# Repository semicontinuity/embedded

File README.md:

Embedded projects.
================================================================================

Projects for AVR microcontrollers.
--------------------------------------------------------------------------------
- [Primitive alarm](../../tree/master/target/alarm-a)
- [Primitive terminal](../../tree/master/target/display)
- [Voltage relay](../../tree/master/target/voltage-relay)
- [Mood lamp - firmware under development](../../tree/master/target/mood-lamp)
- [Primitive motion sensor controller, that works in pair with primitive alarm](../../tree/master/target/motion-sensor-controller/firmware/main)
- [Servo controller - unfinished, no firmware yet](../../tree/master/target/motor-controller/hardware)
- [LED dimmer, controlled via CAN bus](../../tree/master/target/plc-3u-a/firmware/network-led-dimmer)
- [CAN bus router - firmware under development](../../tree/master/target/plc-6u-a/firmware/can_router)
- [Roller shutter controller, controlled via CAN bus](../../tree/master/target/roller-shutter-controller/firmware/main)
- [Humidity meter](../../tree/master/target/plc-3u-b/firmware/humidity-meter)

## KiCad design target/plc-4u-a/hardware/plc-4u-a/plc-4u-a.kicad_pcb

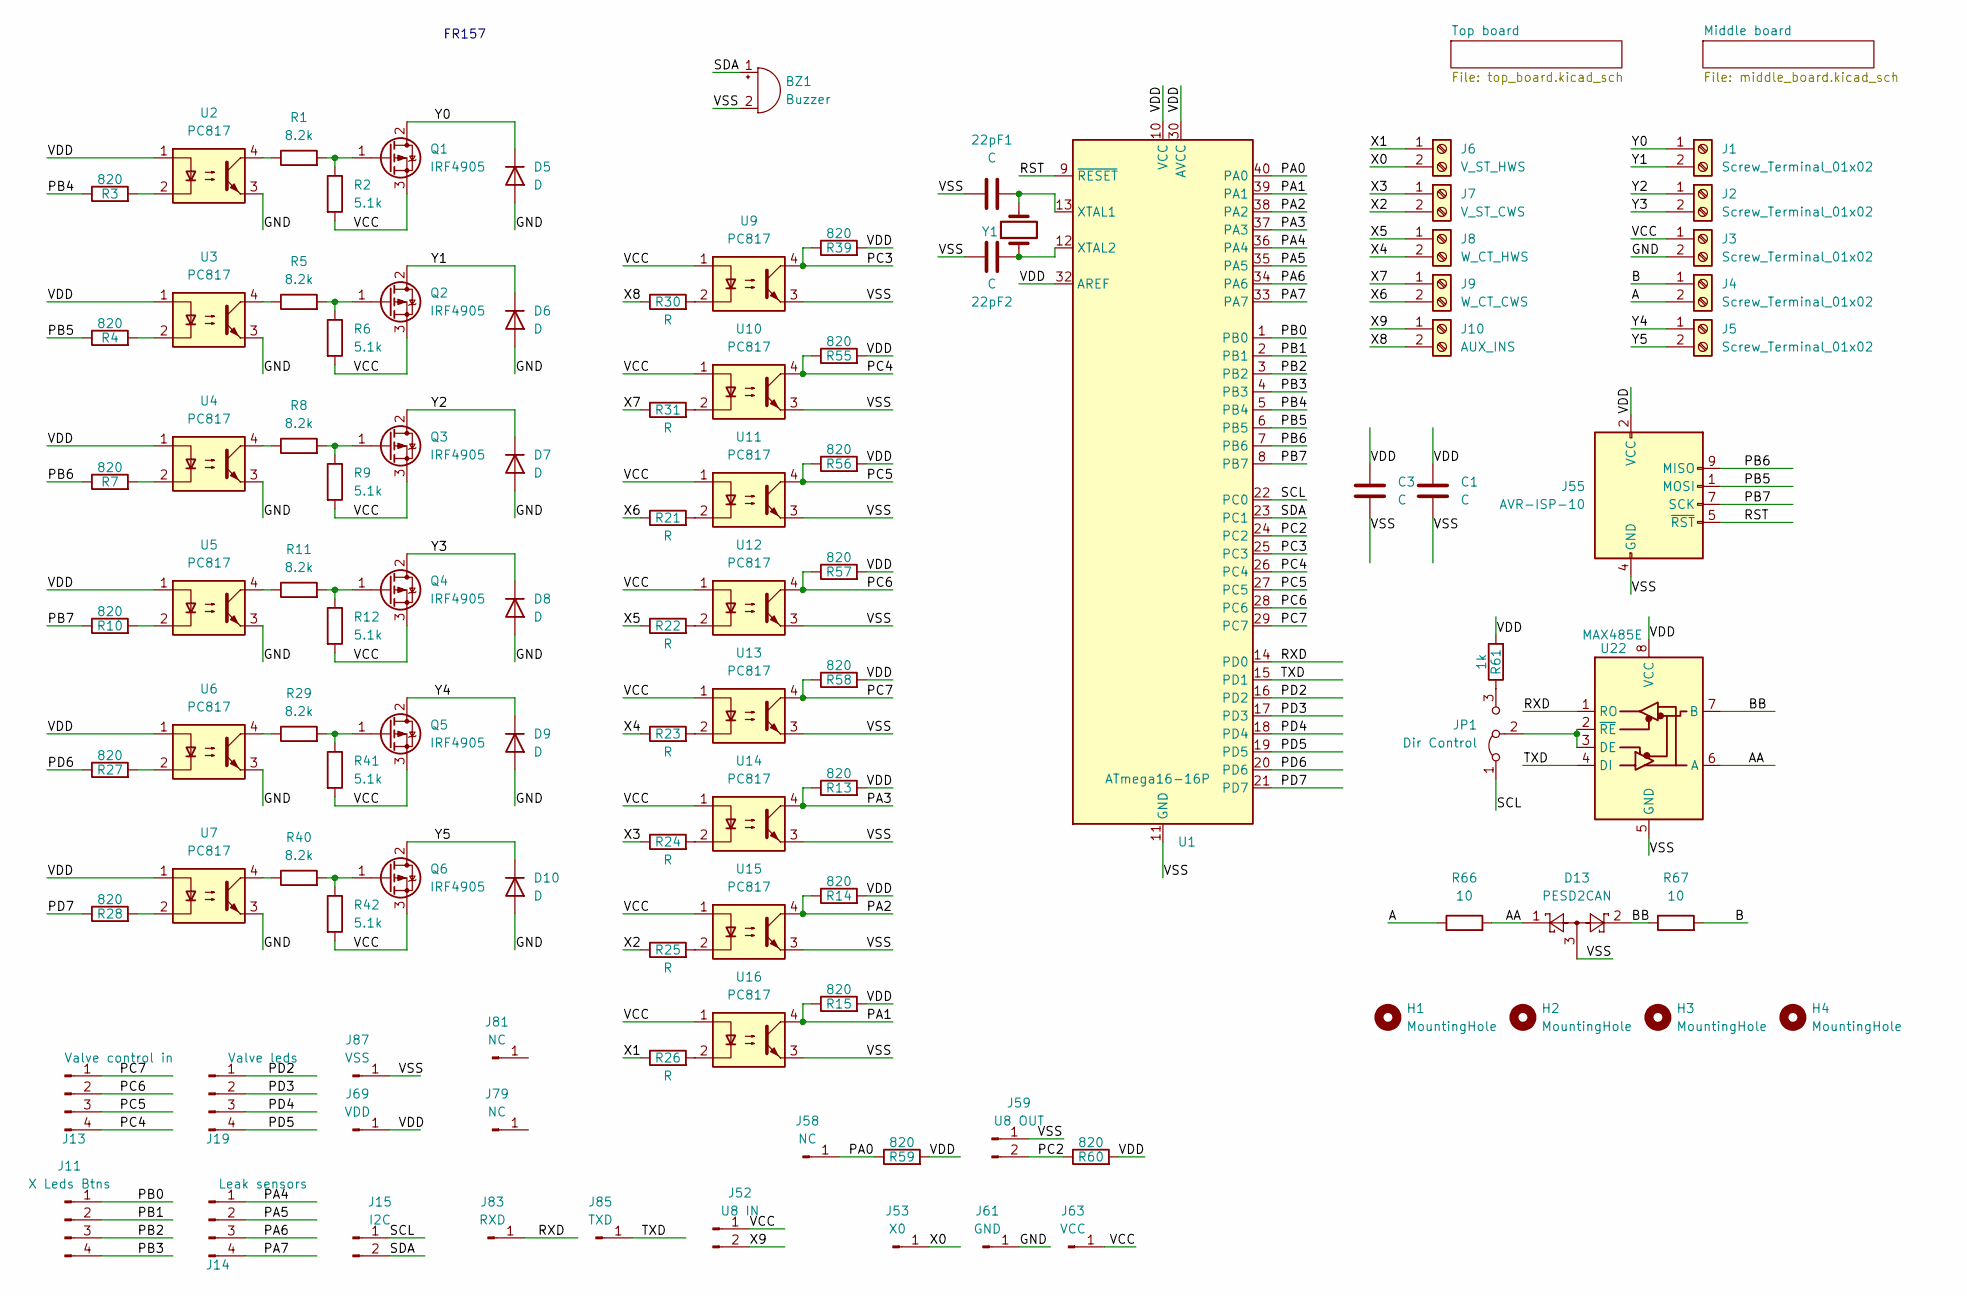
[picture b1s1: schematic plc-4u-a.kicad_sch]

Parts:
22pF1, 22pF2: C; C_0805_2012Metric
BZ1: Buzzer; Buzzer_12x9.5RM7.6
C1, C3: C; C_0805_2012Metric
D5, D6, D7, D8, D9, D10: D; D_DO-41_SOD81_P10.16mm_Horizontal
D13: PESD2CAN; SOT-23
H1, H2, H3, H4: MountingHole; MountingHole_3.2mm_M3
J1, J2, J3, J4, J5: Screw_Terminal_01x02; TerminalBlock_Phoenix_MKDS-1,5-2-5.08_1x02_P5.08mm_Horizont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
J6: V_ST_HWS; TerminalBlock_Phoenix_MKDS-1,5-2-5.08_1x02_P5.08mm_Horizont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
J7: V_ST_CWS; TerminalBlock_Phoenix_MKDS-1,5-2-5.08_1x02_P5.08mm_Horizont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
J8: W_CT_HWS; TerminalBlock_Phoenix_MKDS-1,5-2-5.08_1x02_P5.08mm_Horizont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
J9: W_CT_CWS; TerminalBlock_Phoenix_MKDS-1,5-2-5.08_1x02_P5.08mm_Horizont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
J10: AUX_INS; TerminalBlock_Phoenix_MKDS-1,5-2-5.08_1x02_P5.08mm_Horizont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
J11: X Leds Btns; PinHeader_1x04_P2.54mm_Vertical
J13: Valve control in; PinHeader_1x04_P2.54mm_Vertical
J14: Leak sensors; PinHeader_1x04_P2.54mm_Vertical
J15: I2C; PinHeader_1x02_P2.54mm_Vertical
J19: Valve leds; PinHeader_1x04_P2.54mm_Vertical
J52: U8 IN; PinHeader_1x02_P2.54mm_Vertical
J53: X0; PinHeader_1x01_P2.54mm_Vertical
J55: AVR-ISP-10; IDC-Header_2x05_P2.54mm_Vertical
J58, J79, J81: NC; PinHeader_1x01_P2.54mm_Vertical
J59: U8 OUT; PinHeader_1x02_P2.54mm_Vertical
J61: GND; PinHeader_1x01_P2.54mm_Vertical
J63: VCC; PinHeader_1x01_P2.54mm_Vertical
J69: VDD; PinHeader_1x01_P2.54mm_Vertical
J83: RXD; PinHeader_1x01_P2.54mm_Vertical
J85: TXD; PinHeader_1x01_P2.54mm_Vertical
J87: VSS; PinHeader_1x01_P2.54mm_Vertical
JP1: Dir Control; SolderJumper-3_P1.3mm_Bridged2Bar12_Pad1.0x1.5mm
Q1, Q2, Q3, Q4, Q5, Q6: IRF4905; TO-220-3_Vertical
R1, R5, R8, R11, R29, R40: 8.2k; R_0805_2012Metric
R2, R6, R9, R12, R41, R42: 5.1k; R_0805_2012Metric
R3, R4, R7, R10, R13, R14, R15, R27, R28, R39, R55, R56, R57, R58, R59, R60: 820; R_0805_2012Metric
R21, R22, R23, R24, R25, R26, R30, R31: R; R_1206_3216Metric
R61: 1k; R_0805_2012Metric
R66, R67: 10; R_1206_3216Metric
U1: ATmega16-16P; DIP-40_W15.24mm
U2, U3, U4, U5, U6, U7, U9, U10, U11, U12, U13, U14, U15, U16: PC817; DIP-4_W7.62mm
U22: MAX485E; SOIC-8_3.9x4.9mm_P1.27mm
Y1: Crystal; Crystal_HC49-4H_Vertical

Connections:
/A: J4.2, R66.1
/AA: D13.1, R66.2, U22.6 (A)
/B: J4.1, R67.2
/BB: D13.2, R67.1, U22.7 (B)
/GND: D5.2 (A), D6.2 (A), D7.2 (A), D8.2 (A), D9.2 (A), D10.2 (A), J3.2, J61.1, U2.3, U3.3, U4.3, U5.3, U6.3, U7.3
/PA0: J58.1, R59.1, U1.40 (PA0)
/PA1: R15.1, U1.39 (PA1), U16.4
/PA2: R14.1, U1.38 (PA2), U15.4
/PA3: R13.1, U1.37 (PA3), U14.4
/PA4: J14.1, U1.36 (PA4)
/PA5: J14.2, U1.35 (PA5)
/PA6: J14.3, U1.34 (PA6)
/PA7: J14.4, U1.33 (PA7)
/PB0: J11.1, U1.1 (PB0)
/PB1: J11.2, U1.2 (PB1)
/PB2: J11.3, U1.3 (PB2)
/PB3: J11.4, U1.4 (PB3)
/PB4: R3.1, U1.5 (PB4)
/PB5: J55.1 (MOSI), R4.1, U1.6 (PB5)
/PB6: J55.9 (MISO), R7.1, U1.7 (PB6)
/PB7: J55.7 (SCK), R10.1, U1.8 (PB7)
/PC2: J59.2, R60.1, U1.24 (PC2)
/PC3: R39.1, U1.25 (PC3), U9.4
/PC4: J13.4, R55.1, U1.26 (PC4), U10.4
/PC5: J13.3, R56.1, U1.27 (PC5), U11.4
/PC6: J13.2, R57.1, U1.28 (PC6), U12.4
/PC7: J13.1, R58.1, U1.29 (PC7), U13.4
/PD2: J19.1, U1.16 (PD2)
/PD3: J19.2, U1.17 (PD3)
/PD4: J19.3, U1.18 (PD4)
/PD5: J19.4, U1.19 (PD5)
/PD6: R27.1, U1.20 (PD6)
/PD7: R28.1, U1.21 (PD7)
/RST: J55.5 (~RST), U1.9 (~RESET)
/RXD: J83.1, U1.14 (PD0), U22.1 (RO)
/SCL: J15.1, JP1.1 (A), U1.22 (PC0)
/SDA: BZ1.1 (-), J15.2, U1.23 (PC1)
/TXD: J85.1, U1.15 (PD1), U22.4 (DI)
/VCC: J3.1, J52.1, J63.1, Q1.3 (S), Q2.3 (S), Q3.3 (S), Q4.3 (S), Q5.3 (S), Q6.3 (S), R2.2, R6.2, R9.2, R12.2, R41.2, R42.2, U9.1, U10.1, U11.1, U12.1, U13.1, U14.1, U15.1, U16.1
/VDD: C1.1, C3.1, J55.2 (VCC), J69.1, R13.2, R14.2, R15.2, R39.2, R55.2, R56.2, R57.2, R58.2, R59.2, R60.2, R61.2, U1.10 (VCC), U1.30 (AVCC), U1.32 (AREF), U2.1, U3.1, U4.1, U5.1, U6.1, U7.1, U22.8 (VCC)
/VSS: 22pF1.1, 22pF2.1, BZ1.2 (+), C1.2, C3.2, D13.3, J55.4 (GND), J55.6 (GND), J55.8 (GND), J55.10 (GND), J59.1, J87.1, U1.11 (GND), U1.31 (GND), U9.3, U10.3, U11.3, U12.3, U13.3, U14.3, U15.3, U16.3, U22.5 (GND)
/X0: J6.2, J53.1
/X1: J6.1, R26.1
/X2: J7.2, R25.1
/X3: J7.1, R24.1
/X4: J8.2, R23.1
/X5: J8.1, R22.1
/X6: J9.2, R21.1
/X7: J9.1, R31.1
/X8: J10.2, R30.1
/X9: J10.1, J52.2
/Y0: D5.1 (K), J1.1, Q1.2 (D)
/Y1: D6.1 (K), J1.2, Q2.2 (D)
/Y2: D7.1 (K), J2.1, Q3.2 (D)
/Y3: D8.1 (K), J2.2, Q4.2 (D)
/Y4: D9.1 (K), J5.1, Q5.2 (D)
/Y5: D10.1 (K), J5.2, Q6.2 (D)
unnamed: 22pF1.2, U1.13 (XTAL1), Y1.2
unnamed: 22pF2.2, U1.12 (XTAL2), Y1.1
unnamed: JP1.2 (C), U22.2 (~RE), U22.3 (DE)
unnamed: JP1.3 (B), R61.1
unnamed: Q1.1 (G), R1.2, R2.1
unnamed: Q2.1 (G), R5.2, R6.1
unnamed: Q3.1 (G), R8.2, R9.1
unnamed: Q4.1 (G), R11.2, R12.1
unnamed: Q5.1 (G), R29.2, R41.1
unnamed: Q6.1 (G), R40.2, R42.1
unnamed: R1.1, U2.4
unnamed: R3.2, U2.2
unnamed: R4.2, U3.2
unnamed: R5.1, U3.4
unnamed: R7.2, U4.2
unnamed: R8.1, U4.4
unnamed: R10.2, U5.2
unnamed: R11.1, U5.4
unnamed: R21.2, U11.2
unnamed: R22.2, U12.2
unnamed: R23.2, U13.2
unnamed: R24.2, U14.2
unnamed: R25.2, U15.2
unnamed: R26.2, U16.2
unnamed: R27.2, U6.2
unnamed: R28.2, U7.2
unnamed: R29.1, U6.4
unnamed: R30.2, U9.2
unnamed: R31.2, U10.2
unnamed: R40.1, U7.4

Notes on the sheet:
FR157

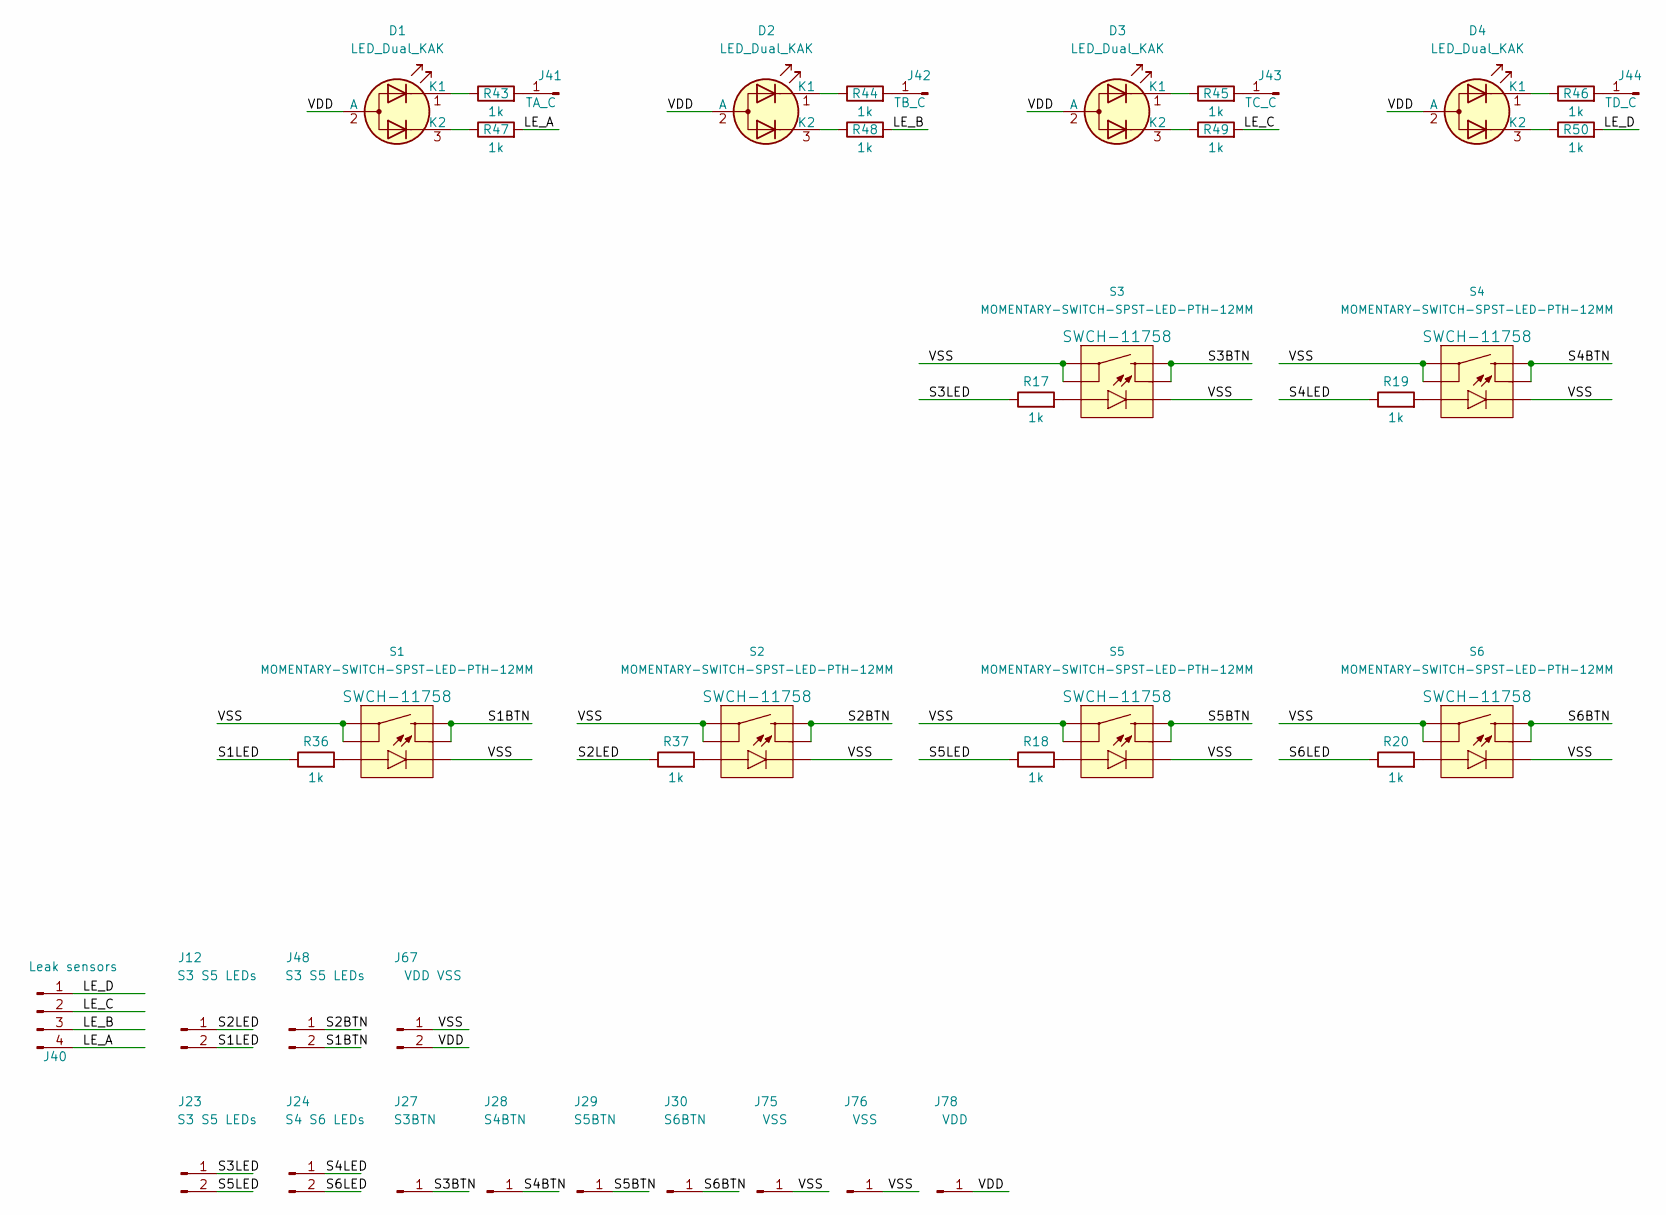
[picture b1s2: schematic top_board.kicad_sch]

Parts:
D1, D2, D3, D4: LED_Dual_KAK; LED_Rectangular_W5.0mm_H2.0mm-3Pins
J12, J23, J48: S3 S5 LEDs; PinHeader_1x02_P2.54mm_Vertical
J24: S4 S6 LEDs; PinHeader_1x02_P2.54mm_Vertical
J27: S3BTN; PinHeader_1x01_P2.54mm_Vertical
J28: S4BTN; PinHeader_1x01_P2.54mm_Vertical
J29: S5BTN; PinHeader_1x01_P2.54mm_Vertical
J30: S6BTN; PinHeader_1x01_P2.54mm_Vertical
J40: Leak sensors; PinHeader_1x04_P2.54mm_Vertical
J41: TA_C; PinHeader_1x01_P2.54mm_Vertical
J42: TB_C; PinHeader_1x01_P2.54mm_Vertical
J43: TC_C; PinHeader_1x01_P2.54mm_Vertical
J44: TD_C; PinHeader_1x01_P2.54mm_Vertical
J67: VDD VSS; PinHeader_1x02_P2.54mm_Vertical
J75, J76: VSS; PinHeader_1x01_P2.54mm_Vertical
J78: VDD; PinHeader_1x01_P2.54mm_Vertical
R17, R18, R19, R20, R36, R37, R43, R44, R45, R46, R47, R48, R49, R50: 1k; R_0805_2012Metric
S1, S2, S3, S4, S5, S6: MOMENTARY-SWITCH-SPST-LED-PTH-12MM; TACTILE_SWITCH_LED_PTH_12MM

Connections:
/Top board/LE_A: J40.4, R47.2
/Top board/LE_B: J40.3, R48.2
/Top board/LE_C: J40.2, R49.2
/Top board/LE_D: J40.1, R50.2
/Top board/S1BTN: J48.2, S1.1, S1.2
/Top board/S1LED: J12.2, R36.1
/Top board/S2BTN: J48.1, S2.1, S2.2
/Top board/S2LED: J12.1, R37.1
/Top board/S3BTN: J27.1, S3.1, S3.2
/Top board/S3LED: J23.1, R17.1
/Top board/S4BTN: J28.1, S4.1, S4.2
/Top board/S4LED: J24.1, R19.1
/Top board/S5BTN: J29.1, S5.1, S5.2
/Top board/S5LED: J23.2, R18.1
/Top board/S6BTN: J30.1, S6.1, S6.2
/Top board/S6LED: J24.2, R20.1
/Top board/VDD: D1.2 (A), D2.2 (A), D3.2 (A), D4.2 (A), J67.2, J78.1
/Top board/VSS: J67.1, J75.1, J76.1, S1.3, S1.4 (1), S1.C, S2.3, S2.4 (1), S2.C, S3.3, S3.4 (1), S3.C, S4.3, S4.4 (1), S4.C, S5.3, S5.4 (1), S5.C, S6.3, S6.4 (1), S6.C
unnamed: D1.1 (K1), R43.1
unnamed: D1.3 (K2), R47.1
unnamed: D2.1 (K1), R44.1
unnamed: D2.3 (K2), R48.1
unnamed: D3.1 (K1), R45.1
unnamed: D3.3 (K2), R49.1
unnamed: D4.1 (K1), R46.1
unnamed: D4.3 (K2), R50.1
unnamed: J41.1, R43.2
unnamed: J42.1, R44.2
unnamed: J43.1, R45.2
unnamed: J44.1, R46.2
unnamed: R17.2, S3.A
unnamed: R18.2, S5.A
unnamed: R19.2, S4.A
unnamed: R20.2, S6.A
unnamed: R36.2, S1.A
unnamed: R37.2, S2.A

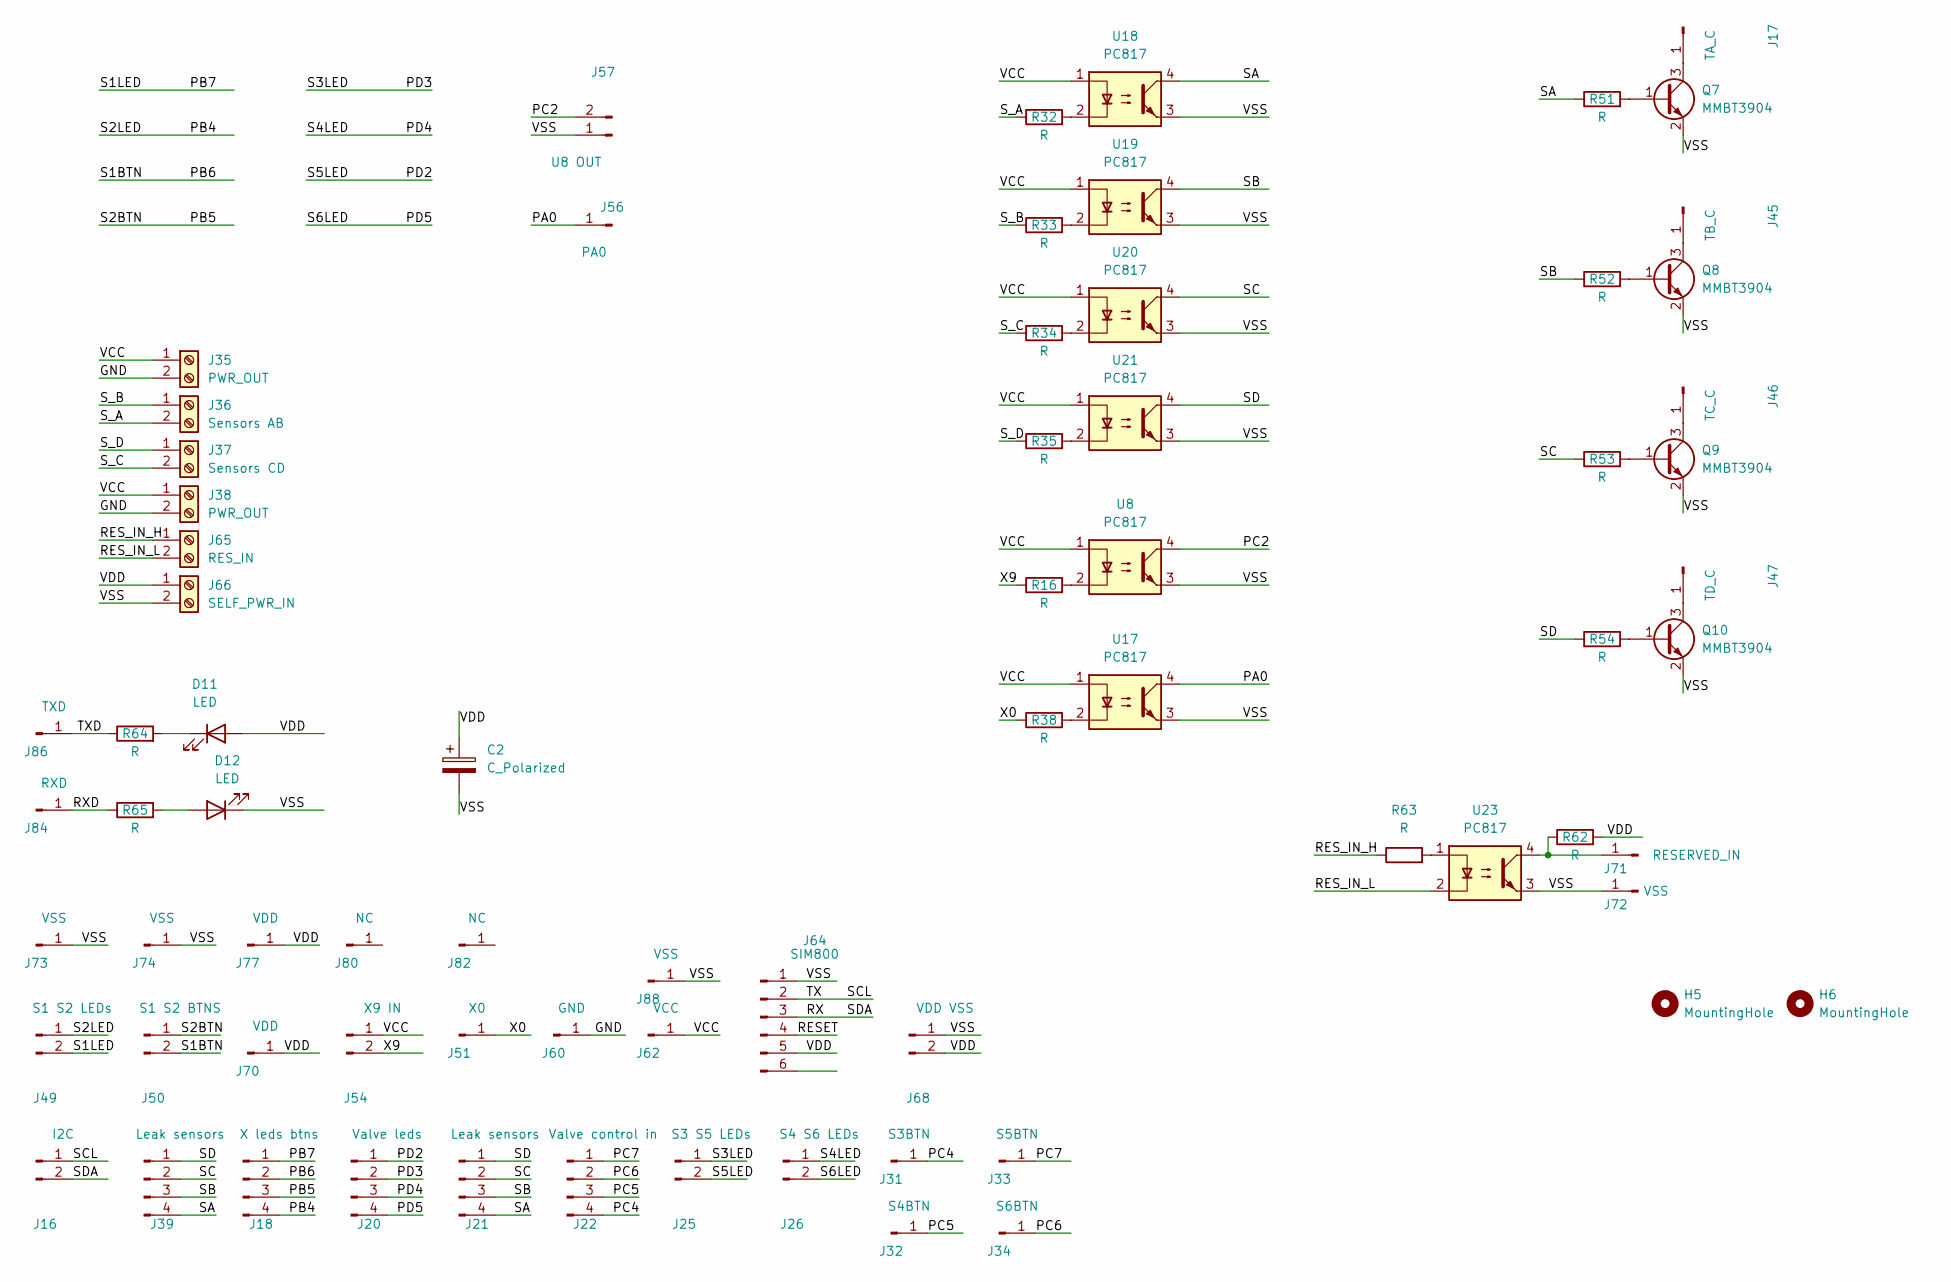
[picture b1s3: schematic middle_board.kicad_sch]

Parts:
C2: C_Polarized; C_1812_4532Metric
D11, D12: LED; LED_D3.0mm
H5, H6: MountingHole; MountingHole_3.2mm_M3
J16: I2C; PinHeader_1x02_P2.54mm_Vertical
J17: TA_C; PinHeader_1x01_P2.54mm_Vertical
J18: X leds btns; PinHeader_1x04_P2.54mm_Vertical
J20: Valve leds; PinHeader_1x04_P2.54mm_Vertical
J21, J39: Leak sensors; PinHeader_1x04_P2.54mm_Vertical
J22: Valve control in; PinHeader_1x04_P2.54mm_Vertical
J25: S3 S5 LEDs; PinHeader_1x02_P2.54mm_Vertical
J26: S4 S6 LEDs; PinHeader_1x02_P2.54mm_Vertical
J31: S3BTN; PinHeader_1x01_P2.54mm_Vertical
J32: S4BTN; PinHeader_1x01_P2.54mm_Vertical
J33: S5BTN; PinHeader_1x01_P2.54mm_Vertical
J34: S6BTN; PinHeader_1x01_P2.54mm_Vertical
J35, J38: PWR_OUT; TerminalBlock_Phoenix_MKDS-1,5-2-5.08_1x02_P5.08mm_Horizont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
J36: Sensors AB; TerminalBlock_Phoenix_MKDS-1,5-2-5.08_1x02_P5.08mm_Horizont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
J37: Sensors CD; TerminalBlock_Phoenix_MKDS-1,5-2-5.08_1x02_P5.08mm_Horizont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
J45: TB_C; PinHeader_1x01_P2.54mm_Vertical
J46: TC_C; PinHeader_1x01_P2.54mm_Vertical
J47: TD_C; PinHeader_1x01_P2.54mm_Vertical
J49: S1 S2 LEDs; PinHeader_1x02_P2.54mm_Vertical
J50: S1 S2 BTNS; PinHeader_1x02_P2.54mm_Vertical
J51: X0; PinHeader_1x01_P2.54mm_Vertical
J54: X9 IN; PinHeader_1x02_P2.54mm_Vertical
J56: PA0; PinHeader_1x01_P2.54mm_Vertical
J57: U8 OUT; PinHeader_1x02_P2.54mm_Vertical
J60: GND; PinHeader_1x01_P2.54mm_Vertical
J62: VCC; PinHeader_1x01_P2.54mm_Vertical
J64: SIM800; PinHeader_1x06_P2.54mm_Vertical
J65: RES_IN; TerminalBlock_Phoenix_MKDS-1,5-2-5.08_1x02_P5.08mm_Horizont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
J66: SELF_PWR_IN; TerminalBlock_Phoenix_MKDS-1,5-2-5.08_1x02_P5.08mm_Horizont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
J68: VDD VSS; PinHeader_1x02_P2.54mm_Vertical
J70, J77: VDD; PinHeader_1x01_P2.54mm_Vertical
J71: RESERVED_IN; PinHeader_1x01_P2.54mm_Vertical
J72, J73, J74, J88: VSS; PinHeader_1x01_P2.54mm_Vertical
J80, J82: NC; PinHeader_1x01_P2.54mm_Vertical
J84: RXD; PinHeader_1x01_P2.54mm_Vertical
J86: TXD; PinHeader_1x01_P2.54mm_Vertical
Q7, Q8, Q9, Q10: MMBT3904; SOT-23
R16, R32, R33, R34, R35, R38: R; R_1206_3216Metric
R51, R52, R53, R54, R62, R64, R65: R; R_0805_2012Metric
R63: R; R_Axial_DIN0309_L9.0mm_D3.2mm_P5.08mm_Vertical
U8, U17, U18, U19, U20, U21, U23: PC817; DIP-4_W7.62mm

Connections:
/Middle board/GND: J35.2, J38.2, J60.1
/Middle board/PA0: J56.1, U17.4
/Middle board/PB4: J18.4, J49.1
/Middle board/PB5: J18.3, J50.1
/Middle board/PB6: J18.2, J50.2
/Middle board/PB7: J18.1, J49.2
/Middle board/PC2: J57.2, U8.4
/Middle board/PC4: J22.4, J31.1
/Middle board/PC5: J22.3, J32.1
/Middle board/PC6: J22.2, J34.1
/Middle board/PC7: J22.1, J33.1
/Middle board/PD2: J20.1, J25.2
/Middle board/PD3: J20.2, J25.1
/Middle board/PD4: J20.3, J26.1
/Middle board/PD5: J20.4, J26.2
/Middle board/RESET: J64.4
/Middle board/RES_IN_H: J65.1, R63.1
/Middle board/RES_IN_L: J65.2, U23.2
/Middle board/RX: J16.2, J64.3
/Middle board/RXD: J84.1, R65.1
/Middle board/SA: J21.4, J39.4, R51.1, U18.4
/Middle board/SB: J21.3, J39.3, R52.1, U19.4
/Middle board/SC: J21.2, J39.2, R53.1, U20.4
/Middle board/SCL: J16.1, J64.2
/Middle board/SD: J21.1, J39.1, R54.1, U21.4
/Middle board/S_A: J36.2, R32.1
/Middle board/S_B: J36.1, R33.1
/Middle board/S_C: J37.2, R34.1
/Middle board/S_D: J37.1, R35.1
/Middle board/TXD: J86.1, R64.1
/Middle board/VCC: J35.1, J38.1, J54.1, J62.1, U8.1, U17.1, U18.1, U19.1, U20.1, U21.1
/Middle board/VDD: C2.1, D11.2 (A), J64.5, J66.1, J68.2, J70.1, J77.1, R62.2
/Middle board/VSS: C2.2, D12.1 (K), J57.1, J64.1, J66.2, J68.1, J72.1, J73.1, J74.1, J88.1, Q7.2 (E), Q8.2 (E), Q9.2 (E), Q10.2 (E), U8.3, U17.3, U18.3, U19.3, U20.3, U21.3, U23.3
/Middle board/X0: J51.1, R38.1
/Middle board/X9: J54.2, R16.1
unnamed: D11.1 (K), R64.2
unnamed: D12.2 (A), R65.2
unnamed: J17.1, Q7.3 (C)
unnamed: J45.1, Q8.3 (C)
unnamed: J46.1, Q9.3 (C)
unnamed: J47.1, Q10.3 (C)
unnamed: J71.1, R62.1, U23.4
unnamed: Q7.1 (B), R51.2
unnamed: Q8.1 (B), R52.2
unnamed: Q9.1 (B), R53.2
unnamed: Q10.1 (B), R54.2
unnamed: R16.2, U8.2
unnamed: R32.2, U18.2
unnamed: R33.2, U19.2
unnamed: R34.2, U20.2
unnamed: R35.2, U21.2
unnamed: R38.2, U17.2
unnamed: R63.2, U23.1

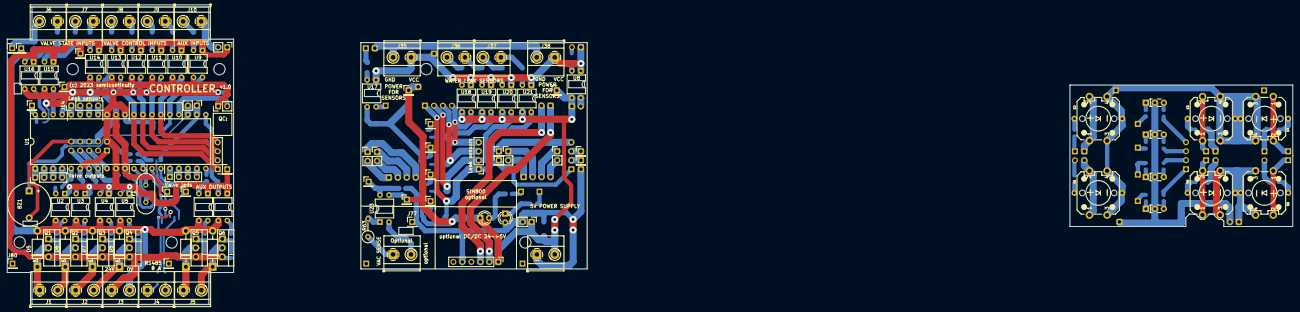
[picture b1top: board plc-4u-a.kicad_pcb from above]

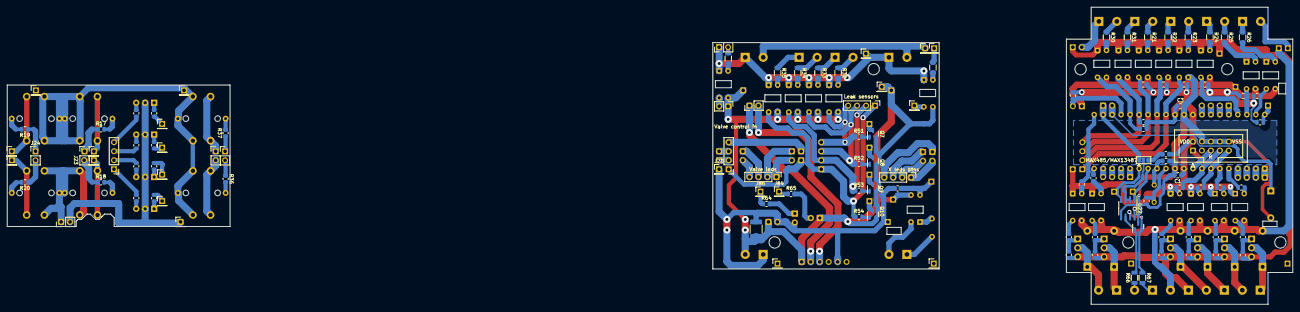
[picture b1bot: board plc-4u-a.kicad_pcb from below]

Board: 2 copper layers, 363.5 x 84.0 mm, 221 parts (113 on the bottom side), 175 nets.

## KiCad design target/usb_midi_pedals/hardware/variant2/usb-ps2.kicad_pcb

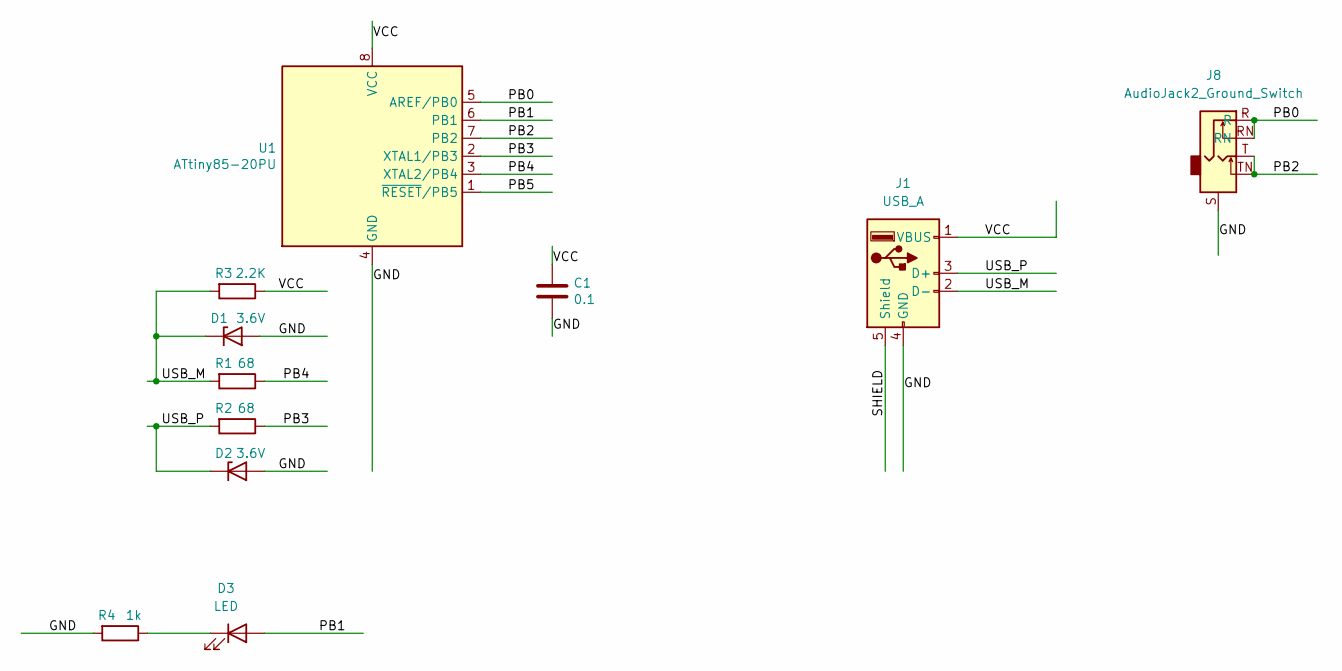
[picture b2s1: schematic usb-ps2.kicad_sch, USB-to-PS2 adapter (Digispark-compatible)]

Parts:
C1: 0.1; C_0805_2012Metric_Pad1.18x1.45mm_HandSolder
D1, D2: 3.6V; D_DO-34_SOD68_P7.62mm_Horizontal
D3: LED; LED_D3.0mm
J1: USB_A; USB_A_CONNFLY_DS1095-WNR0
J8: AudioJack2_Ground_Switch; Jack_3.5mm_CUI_SJ1-3525N_Horizontal
R1, R2: 68; R_Axial_DIN0204_L3.6mm_D1.6mm_P7.62mm_Horizontal
R3: 2.2K; R_0805_2012Metric_Pad1.20x1.40mm_HandSolder
R4: 1k; R_0805_2012Metric_Pad1.20x1.40mm_HandSolder
U1: ATtiny85-20PU; DIP-8_W7.62mm

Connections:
/GND: C1.2, D1.2 (A), D2.2 (A), J1.4 (GND), J8.S, R4.2, U1.4 (GND)
/PB0: J8.R, J8.RN, U1.5 (AREF/PB0)
/PB1: D3.2 (A), U1.6 (PB1)
/PB2: J8.T, J8.TN, U1.7 (PB2)
/PB3: R2.1, U1.2 (XTAL1/PB3)
/PB4: R1.1, U1.3 (XTAL2/PB4)
/PB5: U1.1 (~RESET/PB5)
/SHIELD: J1.5 (Shield)
/USB_M: D1.1 (K), J1.2 (D-), R1.2, R3.2
/USB_P: D2.1 (K), J1.3 (D+), R2.2
/VCC: C1.1, J1.1 (VBUS), R3.1, U1.8 (VCC)
unnamed: D3.1 (K), R4.1

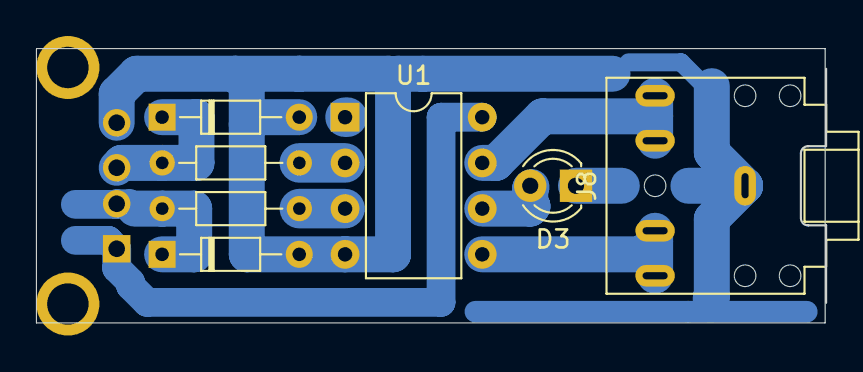
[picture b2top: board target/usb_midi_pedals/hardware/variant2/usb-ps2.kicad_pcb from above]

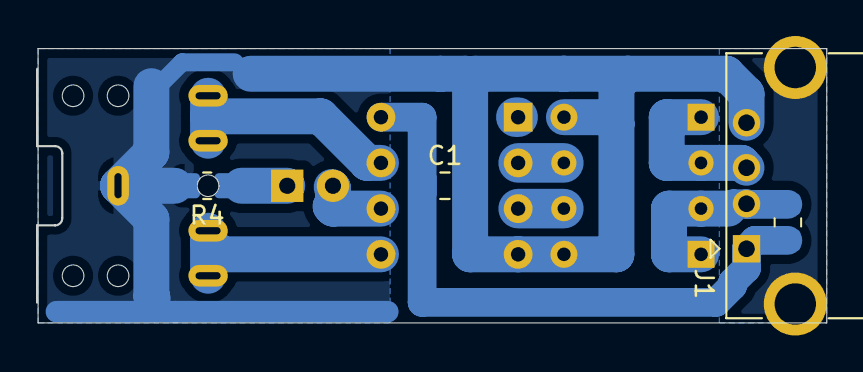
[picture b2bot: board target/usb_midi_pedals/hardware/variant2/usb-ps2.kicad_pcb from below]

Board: 2 copper layers, 43.8 x 15.2 mm, 11 parts (4 on the bottom side), 10 nets.

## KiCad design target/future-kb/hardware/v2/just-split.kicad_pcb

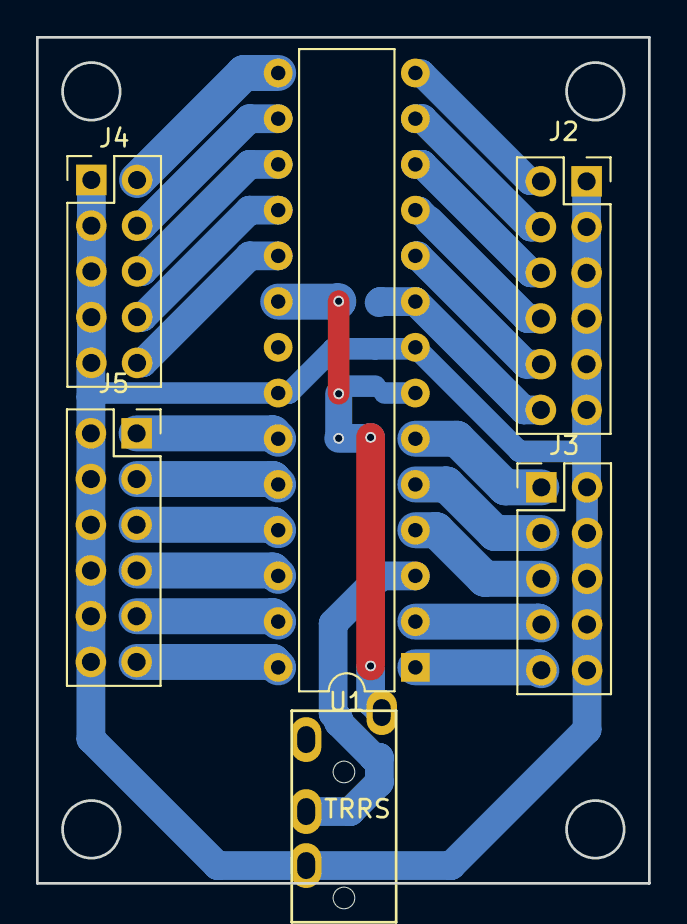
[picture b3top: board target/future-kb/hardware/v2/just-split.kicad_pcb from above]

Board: 2 copper layers, 34.0 x 47.0 mm, 7 parts (1 on the bottom side), 25 nets.

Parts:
C1: 0.1; C_0805_2012Metric_Pad1.18x1.45mm_HandSolder
J1: MJ-4PP-9; MJ-4PP-9_1side
J2, J5: Conn_02x06_Odd_Even; PinSocket_2x06_P2.54mm_Vertical
J3, J4: Conn_02x05_Odd_Even; PinHeader_2x05_P2.54mm_Vertical
U1: ATmega88-20PU; DIP-28_W7.62mm

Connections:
/PB0: J2.2, U1.14 (PB0)
/PB1: J4.2, U1.15 (PB1)
/PB2: J4.4, U1.16 (PB2)
/PB3: J4.6, U1.17 (PB3)
/PB4: J4.8, U1.18 (PB4)
/PB5: J4.10, U1.19 (PB5)
/PB6: J2.12, U1.9 (XTAL1/PB6)
/PB7: J2.10, U1.10 (XTAL2/PB7)
/PC0: J5.1, U1.23 (PC0)
/PC1: J5.3, U1.24 (PC1)
/PC2: J5.5, U1.25 (PC2)
/PC3: J5.7, U1.26 (PC3)
/PC4: J5.9, U1.27 (PC4)
/PC5: J5.11, U1.28 (PC5)
/PD2: J3.5, U1.4 (PD2)
/PD3: J3.3, U1.5 (PD3)
/PD4: J3.1, U1.6 (PD4)
/PD5: J2.8, U1.11 (PD5)
/PD6: J2.6, U1.12 (PD6)
/PD7: J2.4, U1.13 (PD7)
/RESET: J3.9, U1.1 (~RESET/PC6)
/RXD: J3.7, U1.2 (PD0)
/VCC: C1.1, J1.A, U1.7 (VCC), U1.20 (AVCC)
GND: C1.2, J1.B, J2.1, J2.3, J2.5, J2.7, J2.9, J2.11, J3.2, J3.4, J3.6, J3.8, J3.10, J4.1, J4.3, J4.5, J4.7, J4.9, J5.2, J5.4, J5.6, J5.8, J5.10, J5.12, U1.8 (GND), U1.22 (GND)
TXD: J1.C, U1.3 (PD1)

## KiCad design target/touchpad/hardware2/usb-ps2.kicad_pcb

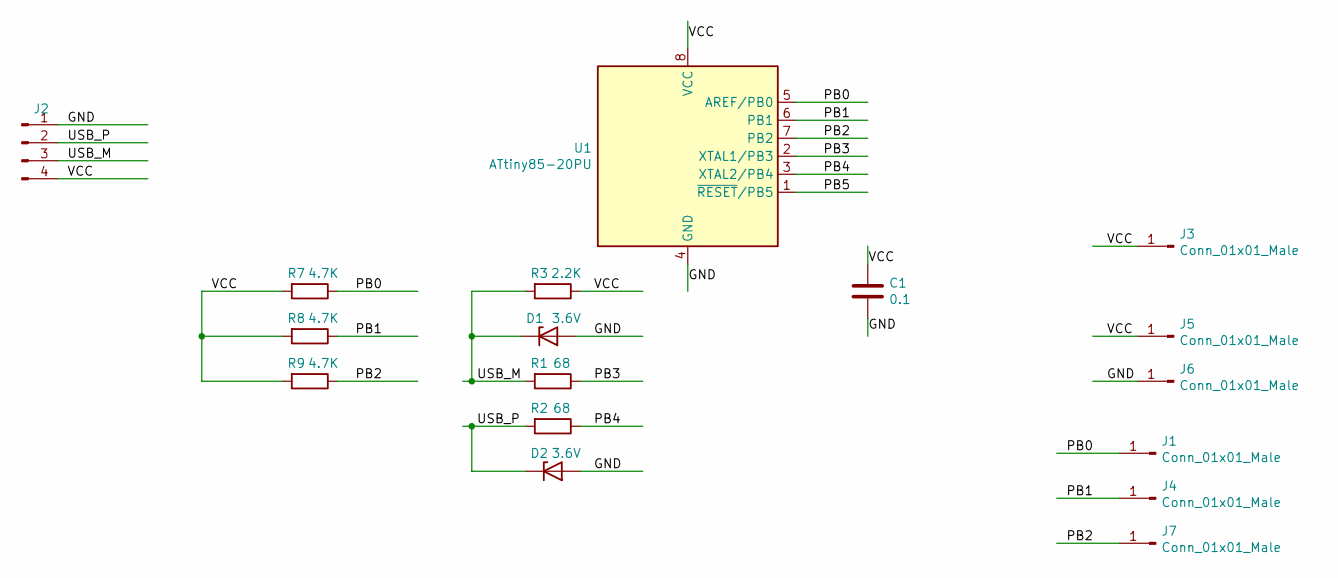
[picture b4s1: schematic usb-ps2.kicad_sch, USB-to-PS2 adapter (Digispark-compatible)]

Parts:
C1: 0.1; C_0805_2012Metric_Pad1.18x1.45mm_HandSolder
D1, D2: 3.6V; D_DO-34_SOD68_P7.62mm_Horizontal
J1, J3, J4, J5, J6, J7: Conn_01x01_Male; PinHeader_1x01_P2.54mm_Vertical
J2: Conn_01x04_Male; PinHeader_1x04_P2.54mm_Vertical
R1, R2: 68; R_Axial_DIN0204_L3.6mm_D1.6mm_P7.62mm_Horizontal
R3: 2.2K; R_0805_2012Metric_Pad1.20x1.40mm_HandSolder
R7, R8, R9: 4.7K; R_0805_2012Metric_Pad1.20x1.40mm_HandSolder
U1: ATtiny85-20PU; DIP-8_W7.62mm

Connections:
/GND: C1.2, D1.2 (A), D2.2 (A), J2.1, J6.1, U1.4 (GND)
/PB0: J1.1, R7.1, U1.5 (AREF/PB0)
/PB1: J4.1, R8.1, U1.6 (PB1)
/PB2: J7.1, R9.1, U1.7 (PB2)
/PB3: R1.1, U1.2 (XTAL1/PB3)
/PB4: R2.1, U1.3 (XTAL2/PB4)
/PB5: U1.1 (~RESET/PB5)
/USB_M: D1.1 (K), J2.3, R1.2, R3.2
/USB_P: D2.1 (K), J2.2, R2.2
/VCC: C1.1, J2.4, J3.1, J5.1, R3.1, R7.2, R8.2, R9.2, U1.8 (VCC)

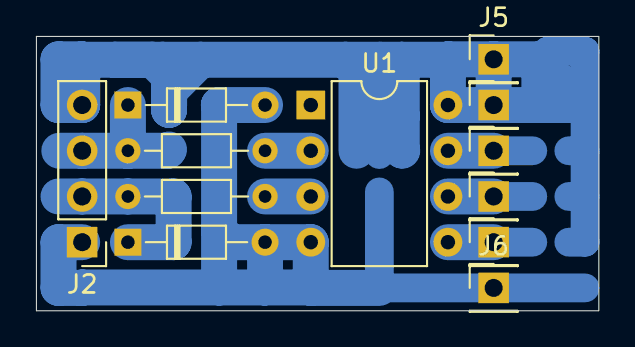
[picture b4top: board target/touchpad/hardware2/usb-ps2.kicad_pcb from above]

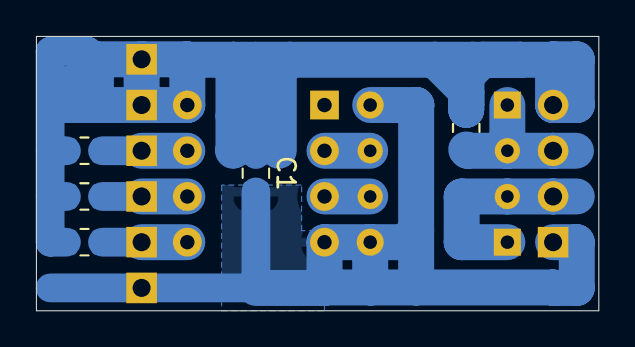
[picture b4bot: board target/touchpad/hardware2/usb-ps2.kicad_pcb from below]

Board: 2 copper layers, 31.2 x 15.2 mm, 17 parts (5 on the bottom side), 9 nets.

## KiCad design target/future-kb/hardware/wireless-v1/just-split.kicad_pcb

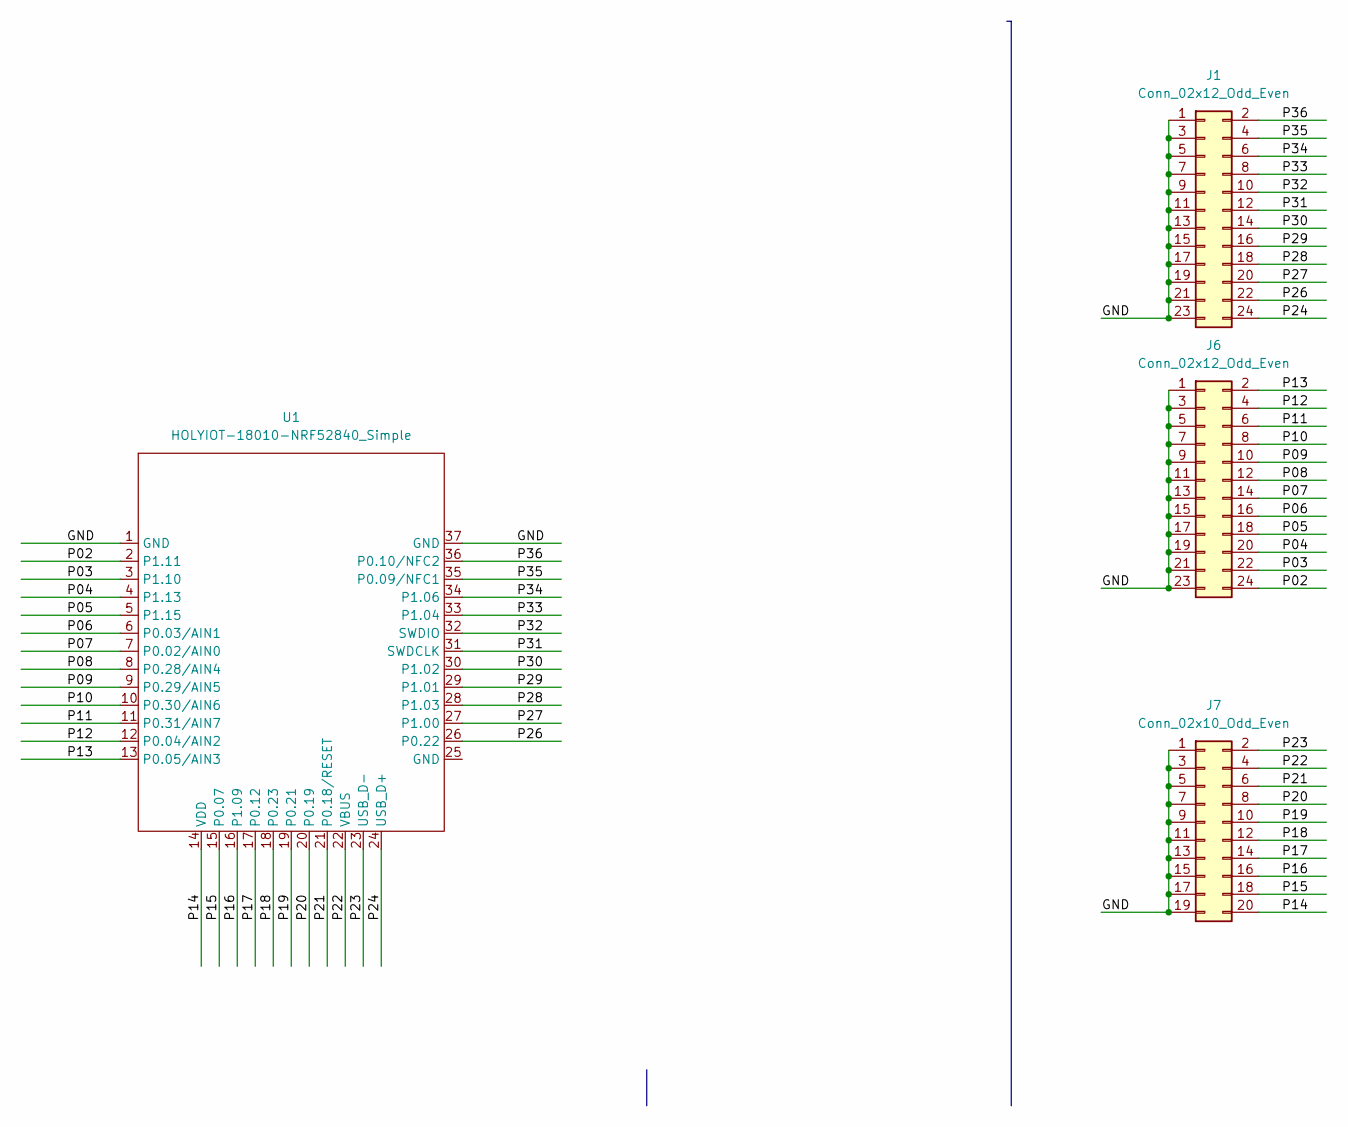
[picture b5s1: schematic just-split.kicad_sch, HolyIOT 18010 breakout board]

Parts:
J1, J6: Conn_02x12_Odd_Even; PinHeader_2x12_P2.54mm_Vertical
J7: Conn_02x10_Odd_Even; PinHeader_2x10_P2.54mm_Vertical
U1: HOLYIOT-18010-NRF52840_Simple; Holyiot-18010-nRF52840

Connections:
/GND: J1.1, J1.3, J1.5, J1.7, J1.9, J1.11, J1.13, J1.15, J1.17, J1.19, J1.21, J1.23, J6.1, J6.3, J6.5, J6.7, J6.9, J6.11, J6.13, J6.15, J6.17, J6.19, J6.21, J6.23, J7.1, J7.3, J7.5, J7.7, J7.9, J7.11, J7.13, J7.15, J7.17, J7.19, U1.1 (GND), U1.37 (GND)
/P02: J6.24, U1.2 (P1.11)
/P03: J6.22, U1.3 (P1.10)
/P04: J6.20, U1.4 (P1.13)
/P05: J6.18, U1.5 (P1.15)
/P06: J6.16, U1.6 (P0.03/AIN1)
/P07: J6.14, U1.7 (P0.02/AIN0)
/P08: J6.12, U1.8 (P0.28/AIN4)
/P09: J6.10, U1.9 (P0.29/AIN5)
/P10: J6.8, U1.10 (P0.30/AIN6)
/P11: J6.6, U1.11 (P0.31/AIN7)
/P12: J6.4, U1.12 (P0.04/AIN2)
/P13: J6.2, U1.13 (P0.05/AIN3)
/P14: J7.20, U1.14 (VDD)
/P15: J7.18, U1.15 (P0.07)
/P16: J7.16, U1.16 (P1.09)
/P17: J7.14, U1.17 (P0.12)
/P18: J7.12, U1.18 (P0.23)
/P19: J7.10, U1.19 (P0.21)
/P20: J7.8, U1.20 (P0.19)
/P21: J7.6, U1.21 (P0.18/RESET)
/P22: J7.4, U1.22 (VBUS)
/P23: J7.2, U1.23 (USB_D-)
/P24: J1.24, U1.24 (USB_D+)
/P26: J1.22, U1.26 (P0.22)
/P27: J1.20, U1.27 (P1.00)
/P28: J1.18, U1.28 (P1.03)
/P29: J1.16, U1.29 (P1.01)
/P30: J1.14, U1.30 (P1.02)
/P31: J1.12, U1.31 (SWDCLK)
/P32: J1.10, U1.32 (SWDIO)
/P33: J1.8, U1.33 (P1.04)
/P34: J1.6, U1.34 (P1.06)
/P35: J1.4, U1.35 (P0.09/NFC1)
/P36: J1.2, U1.36 (P0.10/NFC2)

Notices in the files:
target/plc-4u-a/hardware/plc-4u-a/plc-4u-a.kicad_pcb:
(c) 2023 semicontinuity
